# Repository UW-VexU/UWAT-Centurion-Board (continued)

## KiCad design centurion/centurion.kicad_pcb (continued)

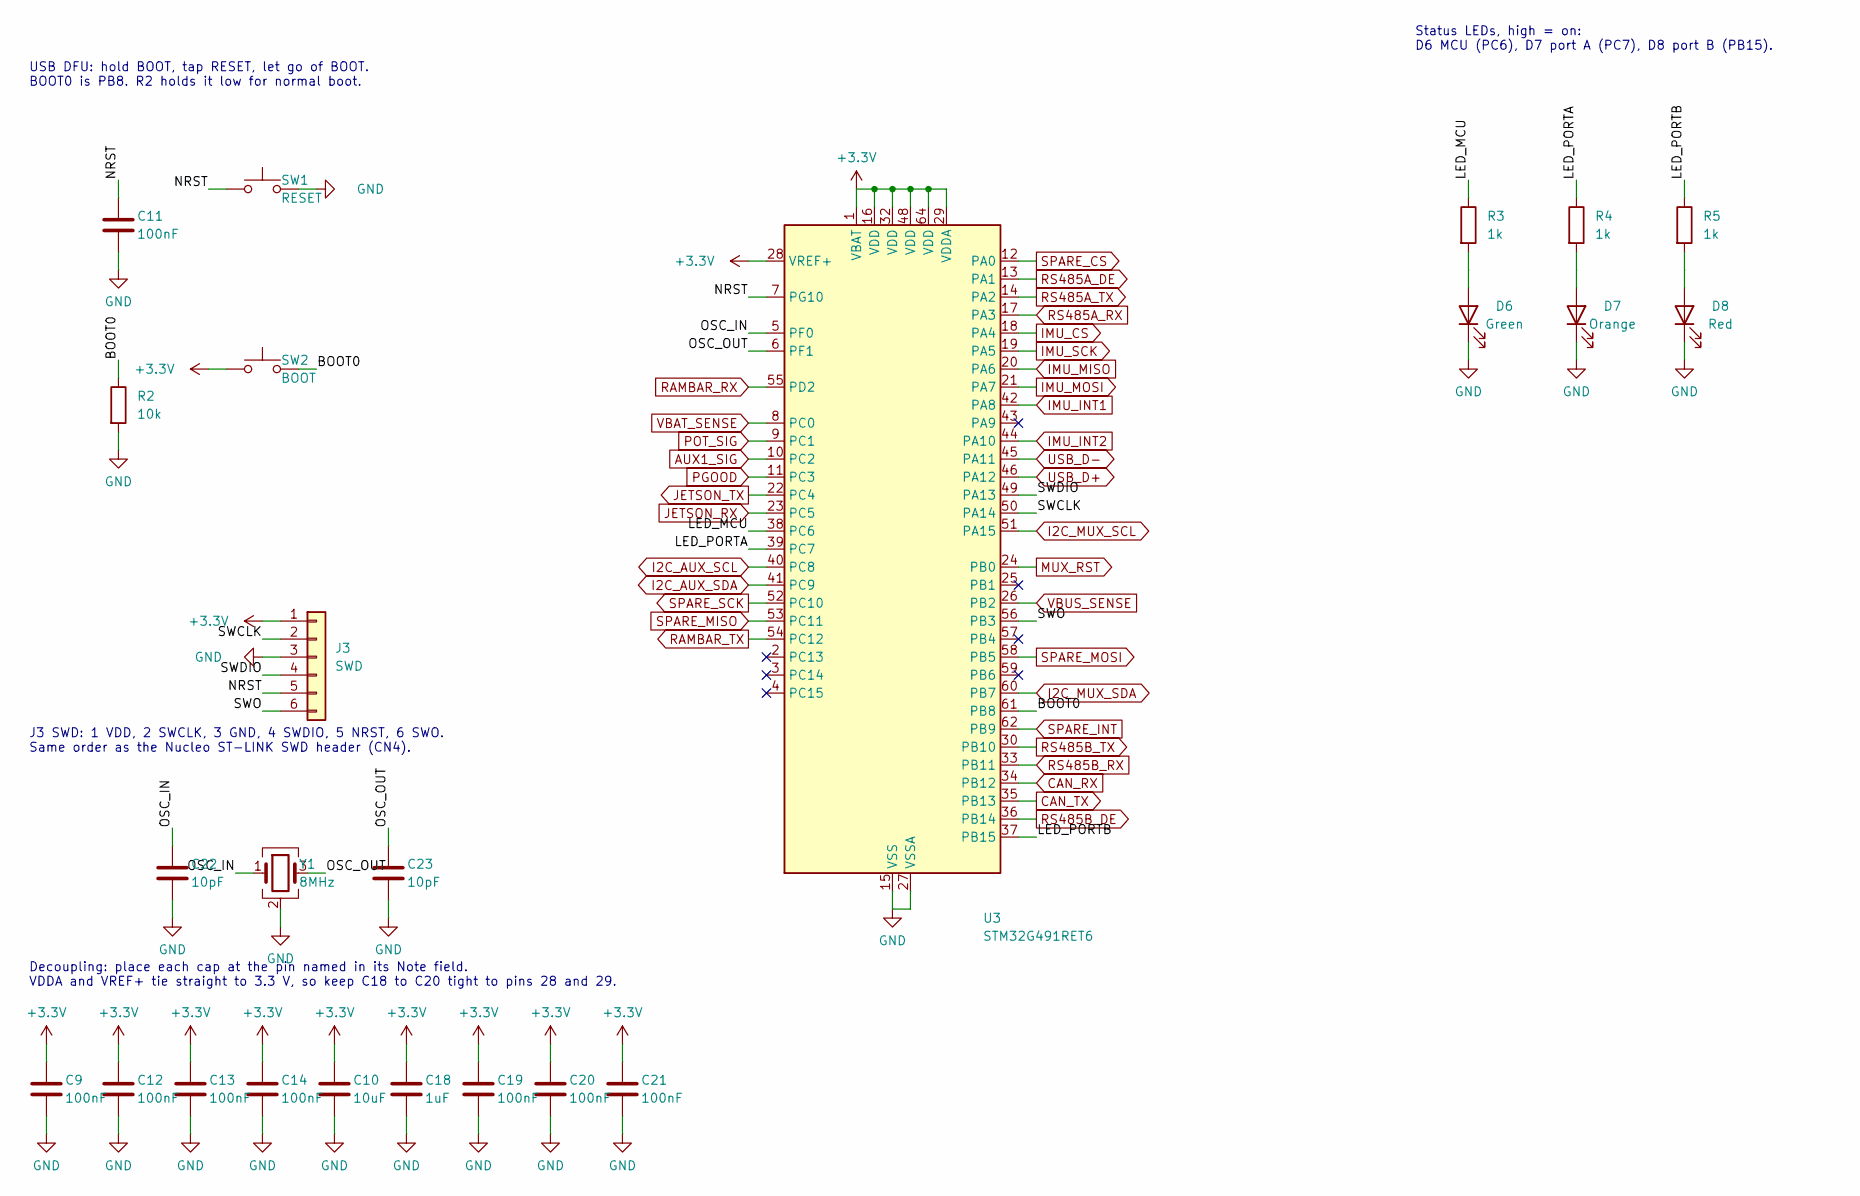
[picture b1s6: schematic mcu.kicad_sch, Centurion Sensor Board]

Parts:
C9, C11, C12, C13, C14, C19, C20, C21: 100nF; C_0805_2012Metric; MPN CC0805KRX7R9BB104
C10: 10uF; C_0805_2012Metric; MPN GRM21BR61E106KA73K
C18: 1uF; C_0805_2012Metric; MPN CC0805KKX7R8BB105
C22, C23: 10pF; C_0805_2012Metric; MPN CC0805JRNPO9BN100
D6: Green; LED_0603_1608Metric; MPN LTST-C191KGKT
D7: Orange; LED_0603_1608Metric; MPN LTST-C191KFKT
D8: Red; LED_0603_1608Metric; MPN LTST-C191KRKT
J3: SWD; PinHeader_1x06_P2.54mm_Vertical; MPN PRPC040SAAN-RC
R2: 10k; R_0805_2012Metric; MPN RC0805FR-0710KL
R3, R4, R5: 1k; R_0805_2012Metric; MPN RC0805FR-071KL
SW1: RESET; SW_SPST_TL3342; MPN TL3342F160QG
SW2: BOOT; SW_SPST_TL3342; MPN TL3342F160QG
U3: STM32G491RET6; LQFP-64_10x10mm_P0.5mm; MPN STM32G491RET6
Y1: 8MHz; Crystal_SMD_3225-4Pin_3.2x2.5mm; MPN ABM8AIG-8.000MHZ-8-V1R-T

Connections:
+3.3V: C9.1, C10.1, C12.1, C13.1, C14.1, C18.1, C19.1, C20.1, C21.1, J3.1, SW2.1, U3.1 (VBAT), U3.16 (VDD), U3.28 (VREF+), U3.29 (VDDA), U3.32 (VDD), U3.48 (VDD), U3.64 (VDD); also elsewhere on the board
/MCU/BOOT0: R2.1, SW2.2, U3.61 (PB8)
/MCU/LED_MCU: R3.1, U3.38 (PC6)
/MCU/LED_PORTA: R4.1, U3.39 (PC7)
/MCU/LED_PORTB: R5.1, U3.37 (PB15)
/MCU/NRST: C11.1, J3.5, SW1.1, U3.7 (PG10)
/MCU/OSC_IN: C22.1, U3.5 (PF0), Y1.1
/MCU/OSC_OUT: C23.1, U3.6 (PF1), Y1.3
/MCU/SWCLK: J3.2, U3.50 (PA14)
/MCU/SWDIO: J3.4, U3.49 (PA13)
/MCU/SWO: J3.6, U3.56 (PB3)
AUX1_SIG: U3.10 (PC2); also elsewhere on the board
CAN_RX: U3.34 (PB12); also elsewhere on the board
CAN_TX: U3.35 (PB13); also elsewhere on the board
GND: C9.2, C10.2, C11.2, C12.2, C13.2, C14.2, C18.2, C19.2, C20.2, C21.2, C22.2, C23.2, D6.1 (K), D7.1 (K), D8.1 (K), J3.3, R2.2, SW1.2, U3.15 (VSS), U3.27 (VSSA), U3.31 (VSS), U3.47 (VSS), U3.63 (VSS), Y1.2 (G), Y1.4 (G); also elsewhere on the board
I2C_AUX_SCL: U3.40 (PC8); also elsewhere on the board
I2C_AUX_SDA: U3.41 (PC9); also elsewhere on the board
I2C_MUX_SCL: U3.51 (PA15); also elsewhere on the board
I2C_MUX_SDA: U3.60 (PB7); also elsewhere on the board
IMU_CS: U3.18 (PA4); also elsewhere on the board
IMU_INT1: U3.42 (PA8); also elsewhere on the board
IMU_INT2: U3.44 (PA10); also elsewhere on the board
IMU_MISO: U3.20 (PA6); also elsewhere on the board
IMU_MOSI: U3.21 (PA7); also elsewhere on the board
IMU_SCK: U3.19 (PA5); also elsewhere on the board
JETSON_RX: U3.23 (PC5); also elsewhere on the board
JETSON_TX: U3.22 (PC4); also elsewhere on the board
MUX_RST: U3.24 (PB0); also elsewhere on the board
unnamed: D6.2 (A), R3.2
unnamed: D7.2 (A), R4.2
unnamed: D8.2 (A), R5.2
PGOOD: U3.11 (PC3); also elsewhere on the board
POT_SIG: U3.9 (PC1); also elsewhere on the board
RAMBAR_RX: U3.55 (PD2); also elsewhere on the board
RAMBAR_TX: U3.54 (PC12); also elsewhere on the board
RS485A_DE: U3.13 (PA1); also elsewhere on the board
RS485A_RX: U3.17 (PA3); also elsewhere on the board
RS485A_TX: U3.14 (PA2); also elsewhere on the board
RS485B_DE: U3.36 (PB14); also elsewhere on the board
RS485B_RX: U3.33 (PB11); also elsewhere on the board
RS485B_TX: U3.30 (PB10); also elsewhere on the board
SPARE_CS: U3.12 (PA0); also elsewhere on the board
SPARE_INT: U3.62 (PB9); also elsewhere on the board
SPARE_MISO: U3.53 (PC11); also elsewhere on the board
SPARE_MOSI: U3.58 (PB5); also elsewhere on the board
SPARE_SCK: U3.52 (PC10); also elsewhere on the board
USB_D+: U3.46 (PA12); also elsewhere on the board
USB_D-: U3.45 (PA11); also elsewhere on the board
VBAT_SENSE: U3.8 (PC0); also elsewhere on the board
VBUS_SENSE: U3.26 (PB2); also elsewhere on the board

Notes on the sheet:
Decoupling: place each cap at the pin named in its Note field. VDDA and VREF+ tie straight to 3.3 V, so keep C18 to C20 tight to pins 28 and 29.
USB DFU: hold BOOT, tap RESET, let go of BOOT. BOOT0 is PB8. R2 holds it low for normal boot.
J3 SWD: 1 VDD, 2 SWCLK, 3 GND, 4 SWDIO, 5 NRST, 6 SWO. Same order as the Nucleo ST-LINK SWD header (CN4).
Status LEDs, high = on: D6 MCU (PC6), D7 port A (PC7), D8 port B (PB15).

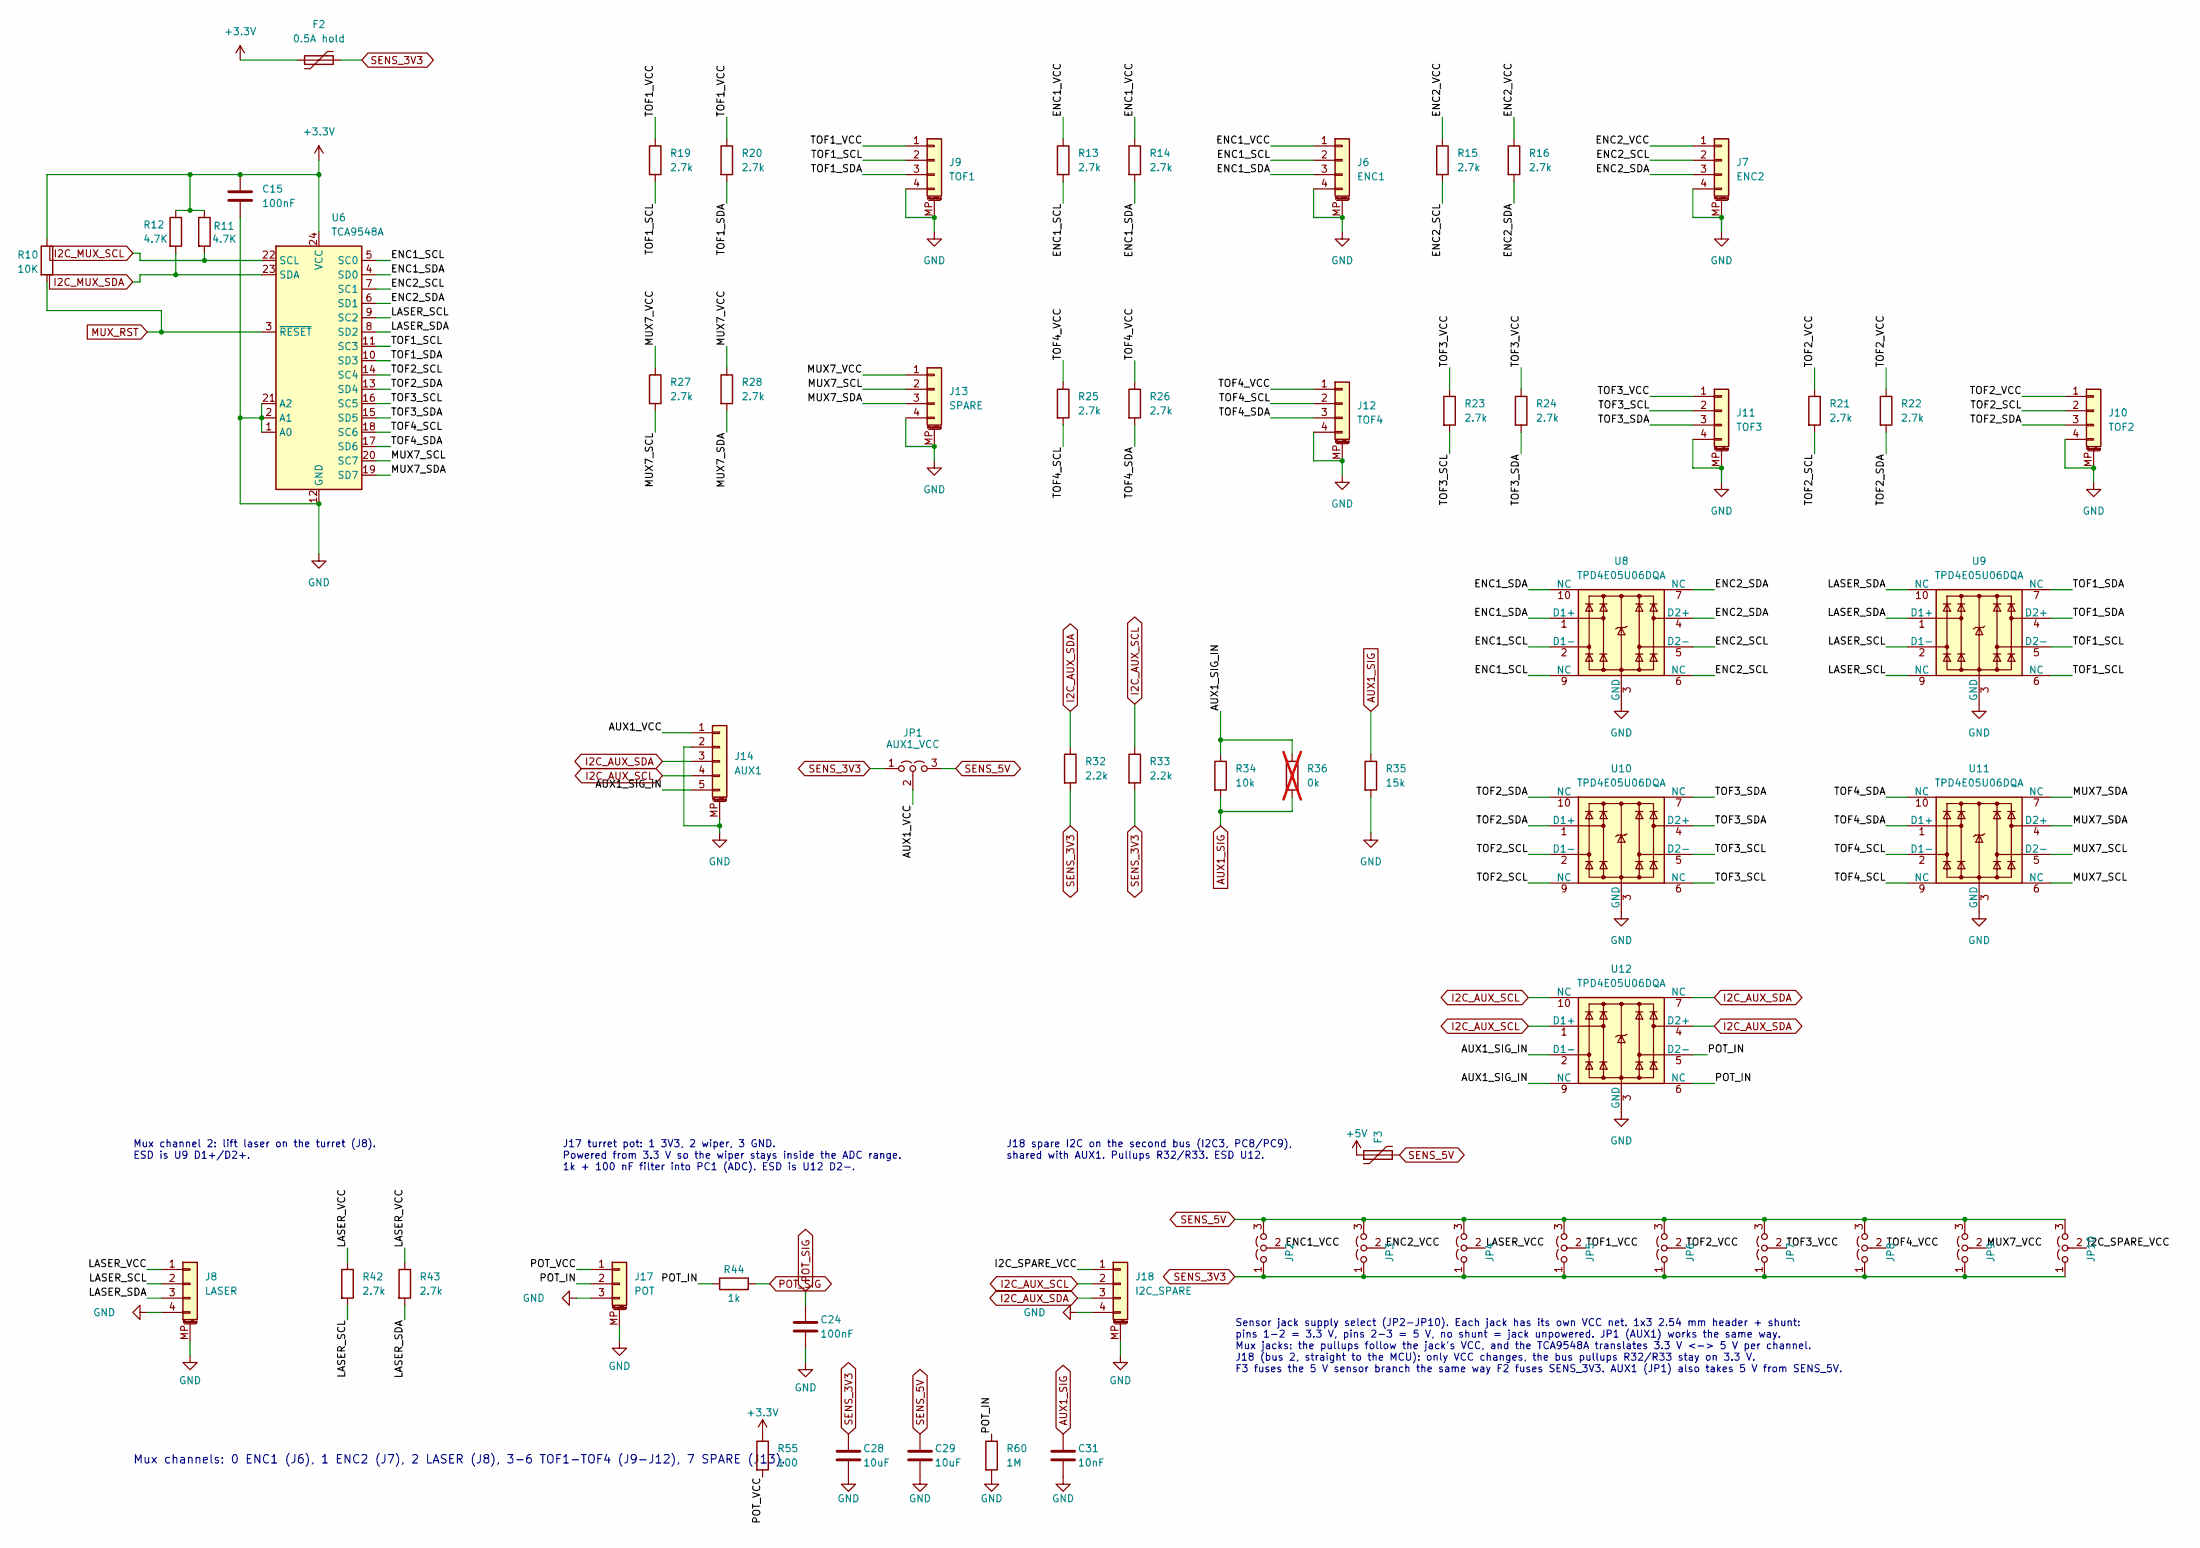
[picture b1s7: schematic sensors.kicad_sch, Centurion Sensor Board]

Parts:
C15, C24: 100nF; C_0805_2012Metric; MPN CC0805KRX7R9BB104
C28, C29: 10uF; C_0805_2012Metric; MPN GRM21BR61E106KA73K
C31: 10nF; C_0805_2012Metric; MPN CC0805KRX7R9BB103
F2, F3: 0.5A hold; Fuse_1206_3216Metric; MPN MF-NSMF050-2
J6: ENC1; JST_GH_SM04B-GHS-TB_1x04-1MP_P1.25mm_Horizontal; MPN SM04B-GHS-TB
J7: ENC2; JST_GH_SM04B-GHS-TB_1x04-1MP_P1.25mm_Horizontal; MPN SM04B-GHS-TB
J8: LASER; JST_GH_SM04B-GHS-TB_1x04-1MP_P1.25mm_Horizontal; MPN SM04B-GHS-TB
J9: TOF1; JST_GH_SM04B-GHS-TB_1x04-1MP_P1.25mm_Horizontal; MPN SM04B-GHS-TB
J10: TOF2; JST_GH_SM04B-GHS-TB_1x04-1MP_P1.25mm_Horizontal; MPN SM04B-GHS-TB
J11: TOF3; JST_GH_SM04B-GHS-TB_1x04-1MP_P1.25mm_Horizontal; MPN SM04B-GHS-TB
J12: TOF4; JST_GH_SM04B-GHS-TB_1x04-1MP_P1.25mm_Horizontal; MPN SM04B-GHS-TB
J13: SPARE; JST_GH_SM04B-GHS-TB_1x04-1MP_P1.25mm_Horizontal; MPN SM04B-GHS-TB
J14: AUX1; JST_GH_SM05B-GHS-TB_1x05-1MP_P1.25mm_Horizontal; MPN SM05B-GHS-TB
J17: POT; JST_GH_SM03B-GHS-TB_1x03-1MP_P1.25mm_Horizontal; MPN SM03B-GHS-TB
J18: I2C_SPARE; JST_GH_SM04B-GHS-TB_1x04-1MP_P1.25mm_Horizontal; MPN SM04B-GHS-TB
JP1: AUX1_VCC; PinHeader_1x03_P2.54mm_Vertical
JP2: ENC1_VCC; PinHeader_1x03_P2.54mm_Vertical
JP3: ENC2_VCC; PinHeader_1x03_P2.54mm_Vertical
JP4: LASER_VCC; PinHeader_1x03_P2.54mm_Vertical
JP5: TOF1_VCC; PinHeader_1x03_P2.54mm_Vertical
JP6: TOF2_VCC; PinHeader_1x03_P2.54mm_Vertical
JP7: TOF3_VCC; PinHeader_1x03_P2.54mm_Vertical
JP8: TOF4_VCC; PinHeader_1x03_P2.54mm_Vertical
JP9: MUX7_VCC; PinHeader_1x03_P2.54mm_Vertical
JP10: I2C_SPARE_VCC; PinHeader_1x03_P2.54mm_Vertical
R10: 10K; R_0805_2012Metric; MPN RC0805FR-0710KL
R11, R12: 4.7K; R_0805_2012Metric; MPN RC0805FR-074K7L
R13, R14, R15, R16, R19, R20, R21, R22, R23, R24, R25, R26, R27, R28, R42, R43: 2.7k; R_0805_2012Metric; MPN RC0805FR-072K7L
R32, R33: 2.2k; R_0805_2012Metric; MPN RC0805FR-072K2L
R34: 10k; R_0805_2012Metric; MPN RC0805FR-0710KL
R35: 15k; R_0805_2012Metric; MPN RC0805FR-0715KL
R36: 0k; R_0805_2012Metric; MPN RC0805JR-070RL; not fitted
R44: 1k; R_0805_2012Metric; MPN RC0805FR-071KL
R55: 100; R_0805_2012Metric; MPN RC0805FR-07100RL
R60: 1M; R_0805_2012Metric; MPN RC0805FR-071ML
U6: TCA9548A; TSSOP-24_4.4x7.8mm_P0.65mm; MPN TCA9548APWR
U8, U9, U10, U11, U12: TPD4E05U06DQA; TI_DQA_USON-10_2.5x1.0mm_P0.5mm; MPN TPD4E05U06QDQARQ1

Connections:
+3.3V: C15.1, F2.1, R10.1, R11.1, R12.1, R55.1, U6.24 (VCC); also elsewhere on the board
+5V: F3.1; also elsewhere on the board
/Sensors/AUX1_SIG_IN: J14.5, R34.1, R36.1, U12.2 (D1-), U12.9 (NC)
/Sensors/AUX1_VCC: J14.1, JP1.2 (C)
/Sensors/ENC1_SCL: J6.2, R13.2, U6.5 (SC0), U8.2 (D1-), U8.9 (NC)
/Sensors/ENC1_SDA: J6.3, R14.2, U6.4 (SD0), U8.1 (D1+), U8.10 (NC)
/Sensors/ENC1_VCC: J6.1, JP2.2 (C), R13.1, R14.1
/Sensors/ENC2_SCL: J7.2, R15.2, U6.7 (SC1), U8.5 (D2-), U8.6 (NC)
/Sensors/ENC2_SDA: J7.3, R16.2, U6.6 (SD1), U8.4 (D2+), U8.7 (NC)
/Sensors/ENC2_VCC: J7.1, JP3.2 (C), R15.1, R16.1
/Sensors/I2C_SPARE_VCC: J18.1, JP10.2 (C)
/Sensors/LASER_SCL: J8.2, R42.2, U6.9 (SC2), U9.2 (D1-), U9.9 (NC)
/Sensors/LASER_SDA: J8.3, R43.2, U6.8 (SD2), U9.1 (D1+), U9.10 (NC)
/Sensors/LASER_VCC: J8.1, JP4.2 (C), R42.1, R43.1
/Sensors/MUX7_SCL: J13.2, R27.2, U6.20 (SC7), U11.5 (D2-), U11.6 (NC)
/Sensors/MUX7_SDA: J13.3, R28.2, U6.19 (SD7), U11.4 (D2+), U11.7 (NC)
/Sensors/MUX7_VCC: J13.1, JP9.2 (C), R27.1, R28.1
/Sensors/POT_IN: J17.2, R44.1, R60.1, U12.5 (D2-), U12.6 (NC)
/Sensors/POT_VCC: J17.1, R55.2
/Sensors/TOF1_SCL: J9.2, R19.2, U6.11 (SC3), U9.5 (D2-), U9.6 (NC)
/Sensors/TOF1_SDA: J9.3, R20.2, U6.10 (SD3), U9.4 (D2+), U9.7 (NC)
/Sensors/TOF1_VCC: J9.1, JP5.2 (C), R19.1, R20.1
/Sensors/TOF2_SCL: J10.2, R21.2, U6.14 (SC4), U10.2 (D1-), U10.9 (NC)
/Sensors/TOF2_SDA: J10.3, R22.2, U6.13 (SD4), U10.1 (D1+), U10.10 (NC)
/Sensors/TOF2_VCC: J10.1, JP6.2 (C), R21.1, R22.1
/Sensors/TOF3_SCL: J11.2, R23.2, U6.16 (SC5), U10.5 (D2-), U10.6 (NC)
/Sensors/TOF3_SDA: J11.3, R24.2, U6.15 (SD5), U10.4 (D2+), U10.7 (NC)
/Sensors/TOF3_VCC: J11.1, JP7.2 (C), R23.1, R24.1
/Sensors/TOF4_SCL: J12.2, R25.2, U6.18 (SC6), U11.2 (D1-), U11.9 (NC)
/Sensors/TOF4_SDA: J12.3, R26.2, U6.17 (SD6), U11.1 (D1+), U11.10 (NC)
/Sensors/TOF4_VCC: J12.1, JP8.2 (C), R25.1, R26.1
AUX1_SIG: C31.1, R34.2, R35.1, R36.2; also elsewhere on the board
GND: C15.2, C24.2, C28.2, C29.2, C31.2, J6.4, J6.MP (MountPin), J7.4, J7.MP (MountPin), J8.4, J8.MP (MountPin), J9.4, J9.MP (MountPin), J10.4, J10.MP (MountPin), J11.4, J11.MP (MountPin), J12.4, J12.MP (MountPin), J13.4, J13.MP (MountPin), J14.2, J14.MP (MountPin), J17.3, J17.MP (MountPin), J18.4, J18.MP (MountPin), R35.2, R60.2, U6.1 (A0), U6.2 (A1), U6.12 (GND), U6.21 (A2), U8.3 (GND), U8.8 (GND), U9.3 (GND), U9.8 (GND), U10.3 (GND), U10.8 (GND), U11.3 (GND), U11.8 (GND), U12.3 (GND), U12.8 (GND); also elsewhere on the board
I2C_AUX_SCL: J14.4, J18.2, R33.1, U12.1 (D1+), U12.10 (NC); also elsewhere on the board
I2C_AUX_SDA: J14.3, J18.3, R32.1, U12.4 (D2+), U12.7 (NC); also elsewhere on the board
I2C_MUX_SCL: R11.2, U6.22 (SCL); also elsewhere on the board
I2C_MUX_SDA: R12.2, U6.23 (SDA); also elsewhere on the board
MUX_RST: R10.2, U6.3 (~RESET); also elsewhere on the board
POT_SIG: C24.1, R44.2; also elsewhere on the board
SENS_3V3: C28.1, F2.2, JP1.1 (A), JP2.1 (A), JP3.1 (A), JP4.1 (A), JP5.1 (A), JP6.1 (A), JP7.1 (A), JP8.1 (A), JP9.1 (A), JP10.1 (A), R32.2, R33.2; also elsewhere on the board
SENS_5V: C29.1, F3.2, JP1.3 (B), JP2.3 (B), JP3.3 (B), JP4.3 (B), JP5.3 (B), JP6.3 (B), JP7.3 (B), JP8.3 (B), JP9.3 (B), JP10.3 (B)

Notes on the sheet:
Mux channel 2: lift laser on the turret (J8). ESD is U9 D1+/D2+.
J17 turret pot: 1 3V3, 2 wiper, 3 GND. Powered from 3.3 V so the wiper stays inside the ADC range. 1k + 100 nF filter into PC1 (ADC). ESD is U12 D2-.
J18 spare I2C on the second bus (I2C3, PC8/PC9), shared with AUX1. Pullups R32/R33. ESD U12.
Mux channels: 0 ENC1 (J6), 1 ENC2 (J7), 2 LASER (J8), 3-6 TOF1-TOF4 (J9-J12), 7 SPARE (J13).
Sensor jack supply select (JP2-JP10). Each jack has its own VCC net. 1x3 2.54 mm header + shunt: pins 1-2 = 3.3 V, pins 2-3 = 5 V, no shunt = jack unpowered. JP1 (AUX1) works the same way. Mux jacks: the pullups follow the jack's VCC, and the TCA9548A translates 3.3 V <-> 5 V per channel. J18 (bus 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

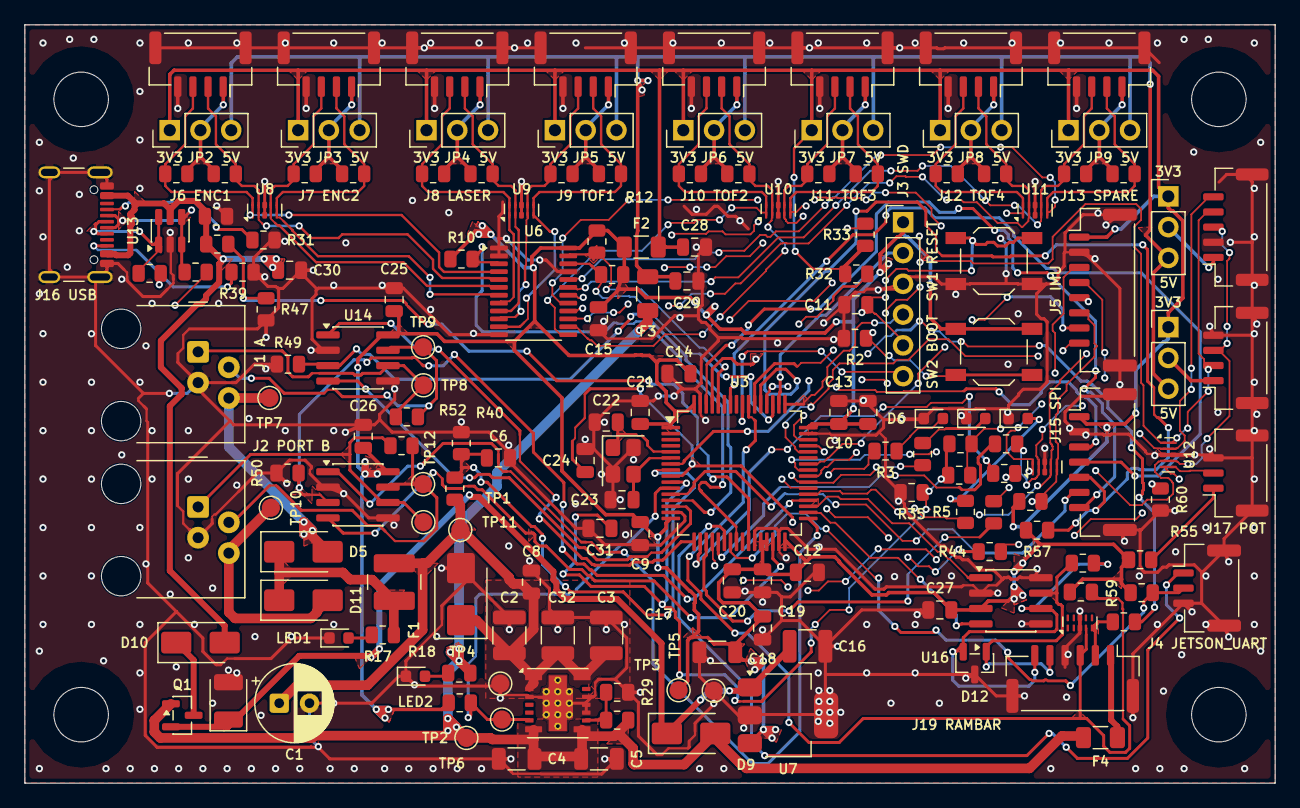
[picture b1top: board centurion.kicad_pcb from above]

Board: 4 copper layers, 103.2 x 62.6 mm, 169 parts (0 on the bottom side), 107 nets.

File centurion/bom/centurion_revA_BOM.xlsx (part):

Centurion Sensor Board, Bill of Materials, Rev A (STM32G491 + TCA9548A + TCAN33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
UWAT VEXU. DigiKey Canada stock and CAD price breaks, read from digikey.ca on N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
Boards to build |  | 6 | Edit the yellow cells. Type your own quantity in the yellow Your order qty colu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
Ref | Block | Description | Manufacturer | Mfr part number | DigiKey part number | Qty per board | Spares | Needed (boards x qty + spares) | Your order qty (optional) | Order qty | Unit price at order qty (CAD) | Order cost (CAD) | Next price break (qty) | Unit price at next break (CAD) | Tip | DigiKey stock | DigiKey Canada link | Notes | On hand (left from earlier orders) | Earlier order
C1 | Power | Aluminum electrolytic, 47 µF 50 V, 6.3 mm radial | Panasonic | EEU-FR1H470 | P124235-ND | 1 | 0 | 6 |  | 0 | 0.7 | 0 |  |  |  | 26276 | https://www.digikey.ca/en/products/detail/panasonic-industry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 |  | 8 | powerJackal
C2, C3, C16, C32 | Power | Ceramic capacitor, 10 µF 50 V X7R, 1210 | Samsung Electro-Mechanics | CL32B106KBJNNNE | 1276-3387-1-ND | 4 | 2 | 26 |  | 0 | 0.63600000000000001 | 0 |  |  |  | 742985 | https://www.digikey.ca/en/products/detail/samsung-electro-me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 | C2, C3, C32: buck input ceramics at U1 VIN (TI asks for 20 uF effective). C16: 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 | 26 | powerJackal, stellaNova
C4, C5, C17 | Power | Ceramic capacitor, 47 µF 10 V X5R, 1206 | Murata | GRM31CR61A476ME15L | 490-5528-1-ND | 3 | 2 | 20 |  | 0 | 0.36199999999999999 | 0 |  |  |  | 180907 | https://www.digikey.ca/en/products/detail/murata-electronics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 |  | 42 | powerJackal
C6, C8, C9, C11, C12, C13, C14, C15, C19, C20, C21, C24, C25, C26, C27, C30 | Power, MCU, Sensor ports, Smart ports | Ceramic capacitor, 100 nF 50 V X7R, 0805 | Yageo | CC0805KRX7R9BB104 | 311-1140-1-ND | 16 | 2 | 98 | 10 | 10 | 0.14599999999999999 | 1.46 | 50 | 0.1018 |  | 4955773 | https://www.digikey.ca/en/products/detail/yageo/CC0805KRX7R9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 | Place at NRST pin 7. Place at U14/U15 pin 8. Place at VBAT pin 1. Place at VDD 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 | 88 | powerJackal
D4 | Power | TVS diode, 16 V standoff, unidirectional, SMB | Littelfuse | SMBJ16A | SMBJ16ALFCT-ND | 1 | 1 | 7 |  | 0 | 0.79 | 0 |  |  |  | 25785 | https://www.digikey.ca/en/products/detail/littelfuse-inc/SMB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 |  | 8 | powerJackal
D9, D10 | Power | Schottky diode, 40 V 1 A, SMA | Vishay | SS14-E3/61T | SS14-E3/61TGICT-ND | 2 | 1 | 13 | 2 | 2 | 0.7 | 1.4 | 10 | 0.42499999999999999 |  | 178712 | https://www.digikey.ca/en/products/detail/vishay-general-sem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 |  | 11 | powerJackal
F1 | Power | Polyfuse, 1.5 A hold, 33 V, 2016 | Littelfuse | 2016L150/33DR | 18-2016L150/33DRCT-ND | 1 | 1 | 7 |  | 0 | 1.0980000000000001 | 0 |  |  |  | 29235 | https://www.digikey.ca/en/products/detail/littelfuse-inc/201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 |  | 8 | powerJackal
J16 | Power | USB-C receptacle, USB 2.0, 16 pin | GCT | USB4105-GF-A | 2073-USB4105-GF-ACT-ND | 1 | 0 | 6 |  | 0 | 1.19 | 0 |  |  |  | 85103 | https://www.digikey.ca/en/products/detail/gct/USB4105-GF-A/11198441 |  | 15 | powerJackal, stellaNova
Q1 | Power | P-channel MOSFET, -30 V, SOT-23 (USB power switch) | Alpha & Omega Semiconductor | AO3401A | 785-1001-1-ND | 1 | 1 | 7 |  | 0 | 0.82 | 0 |  |  |  | 319128 | https://www.digikey.ca/en/products/detail/alpha-omega-semico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 | USB power switch. On only while the 5 V rail is down, so USB powers the board o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 | 8 | powerJackal
R1 | Power | Resistor, 100 kΩ 1%, 0805 | Yageo | RC0805FR-07100KL | 311-100KCRCT-ND | 1 | 2 | 8 | 25 | 25 | 4.48E-2 | 1.1199999999999999 | 50 | 3.6799999999999999E-2 |  | 357376 | https://www.digikey.ca/en/products/detail/yageo/RC0805FR-071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 |  | 0
R18, R32, R33 | Power, Sensor ports | Resistor, 2.2 kΩ 1%, 0805 | Yageo | RC0805FR-072K2L | 311-2.20KCRCT-ND | 3 | 2 | 20 |  | 0 | 5.3999999999999999E-2 | 0 |  |  |  | 374622 | https://www.digikey.ca/en/products/detail/yageo/RC0805FR-072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 | R18: LED2. R32, R33: bus 2 (I2C3) pullups, 2.2k so two cables still meet 400 kH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 | 98 | powerJackal
R29 | Power | Resistor, 2.49 kΩ 1%, 0805 (5 V feedback) | Yageo | RC0805FR-072K49L | 311-2.49KCRCT-ND | 1 | 2 | 8 |  | 0 | 0.17 | 0 |  |  |  | 1178164 | https://www.digikey.ca/en/products/detail/yageo/RC0805FR-072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 | RFBB, sets 5.0 V | 108 | powerJackal
R31, R37, R48 | Power | Resistor, 5.1 kΩ 1%, 0805 | Stackpole Electronics | RMCF0805FT5K10 | RMCF0805FT5K10CT-ND | 3 | 2 | 20 |  | 0 | 4.2999999999999997E-2 | 0 |  |  |  | 98354 | https://www.digikey.ca/en/products/detail/stackpole-electron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 |  | 246 | powerJackal
R40 | Power | Resistor, 22 kΩ 1%, 0805 | Yageo | RC0805FR-0722KL | 311-22.0KCRCT-ND | 1 | 2 | 8 | 25 | 25 | 4.48E-2 | 1.1199999999999999 | 50 | 3.6799999999999999E-2 |  | 186895 | https://www.digikey.ca/en/products/detail/yageo/RC0805FR-072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 | Battery sense, 100k over 22k: 3.3 V full scale is 18.3 V. | 0
U1 | Power | 5 V step-down power module, 2 A, B3QFN-14 | Texas Instruments | TPSM53602RDAR | 296-TPSM53602RDARCT-ND | 1 | 0 | 6 | 3 | 3 | 11.13 | 33.39 | 5 | 10.72 |  | 2786 | https://www.digikey.ca/en/products/detail/texas-instruments/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 | EN tied to VIN. DNC pins 4, 5 and V5V (13) stay unconnected. | 3 | powerJackal
U7 | Power | LDO regulator, 3.3 V 1 A, SOT-223 | Microchip Technology | MCP1826ST-3302E/DB | MCP1826ST-3302E/DBCT-ND | 1 | 0 | 6 |  | 0 | 1.44 | 0 |  |  |  | 39535 | https://www.digikey.ca/en/products/detail/microchip-technolo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 | Drawn with the AP7361C-33E symbol. Same SOT-223 pinout: 1 IN, 2 GND and tab, 3 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 | 8 | powerJackal
U13 | Power | USB ESD protection, SOT-23-6 | STMicroelectronics | USBLC6-2SC6 | 497-5235-1-ND | 1 | 1 | 7 |  | 0 | 0.8 | 0 |  |  |  | 63343 | https://www.digikey.ca/en/products/detail/stmicroelectronics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 |  | 15 | powerJackal, stellaNova
D5, D11 | Smart ports | Schottky diode, 40 V 3 A, SMA (smart port OR diodes) | Diodes Incorporated | B340A-13-F | B340A-FDICT-ND | 2 | 1 | 13 |  | 0 | 0.497 | 0 |  |  |  | 254159 | https://www.digikey.ca/en/products/detail/diodes-incorporate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 |  | 21 | powerJackal
J1, J2 | Smart ports | Smart port jack, 4P4C modular, right angle, through hole | Molex | 0955012441 | WM5568-ND | 2 | 0 | 12 |  | 0 | 1.2929999999999999 | 0 |  |  |  | 4151 | https://www.digikey.ca/en/products/detail/molex/0955012441/1835860 | Pin map assumes the usual black, red, green, yellow order. Check with a meter. | 15 | powerJackal, stellaNova
U14, U15 | Smart ports | RS-485 transceiver, half duplex, 3.3 V, ±65 V fault protected, 2 Mbps, SOIC-8 | Analog Devices | MAX33071EASA+ | 505-MAX33071EASA+-ND | 2 | 0 | 12 | 5 | 5 | 12.3 | 61.5 | 10 | 9.5039999999999996 |  | 2946 | https://www.digikey.ca/en/products/detail/analog-devices-inc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 | RE tied low: the receiver is always on, so the MCU hears its own echo when send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 | 7 | stellaNova
C10, C28, C29 | MCU, Sensor ports | Ceramic capacitor, 10 µF 25 V X5R, 0805 | Murata | GRM21BR61E106KA73K | 490-16824-1-ND | 3 | 2 | 20 | 11 | 11 | 0.14099999999999999 | 1.5509999999999999 | 50 | 9.98E-2 |  | 88143 | https://www.digikey.ca/en/products/detail/murata-electronics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 | C10: bulk at U3. C28, C29: bulk on SENS_3V3 and SENS_5V after F2/F3. | 9 | stellaNova
C18 | MCU | Ceramic capacitor, 1 µF 25 V X7R, 0805 | Yageo | CC0805KKX7R8BB105 | 311-1456-1-ND | 1 | 2 | 8 |  | 0 | 0.42 | 0 |  |  |  | 327549 | https://www.digikey.ca/en/products/detail/yageo/CC0805KKX7R8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 | Place at VDDA pin 29 | 18 | powerJackal
D6, LED1, LED2 | MCU, Power | LED, green, 0603 | Lite-On | LTST-C191KGKT | 160-1446-1-ND | 3 | 2 | 20 | 13 | 13 | 0.16500000000000001 | 2.145 | 100 | 0.1132 |  | 2712898 | https://www.digikey.ca/en/products/detail/liteon/LTST-C191KG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 |  | 7 | stellaNova
D7 | MCU | LED, orange, 0603 | Lite-On | LTST-C191KFKT | 160-1445-1-ND | 1 | 2 | 8 | 1 | 1 | 0.22 | 0.22 | 10 | 0.155 |  | 195728 | https://www.digikey.ca/en/products/detail/liteon/LTST-C191KF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 |  | 7 | stellaNova
D8 | MCU | LED, red, 0603 | Lite-On | LTST-C191KRKT | 160-1447-1-ND | 1 | 2 | 8 | 1 | 1 | 0.24 | 0.24 | 10 | 0.16500000000000001 |  | 1354761 | https://www.digikey.ca/en/products/detail/liteon/LTST-C191KR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 |  | 7 | stellaNova
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
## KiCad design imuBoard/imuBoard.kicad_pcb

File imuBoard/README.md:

# centurion IMU board (imuBoard)

A small board that carries a Bosch BMI270 IMU. It plugs into centurion's J5 with a straight JST GH 8-pin cable. Designed 2026-11-04, rev 1.0.

| | |
|---|---|
| Size | 38 x 24 mm, 2 layers, 1.6 mm, GND pour on both sides |
| Mounting | Two #8-32 holes (4.5 mm), 25.4 mm (1 in) apart, so they land on VEX's 0.5 in hole grid. Not tied to GND, with a 5 mm copper keepout for the screw heads |
| IMU | U1 Bosch BMI270, 4-wire SPI, 10 MHz max |
| Connector | J1 JST GH 8-pin, vertical (BM08B-GHS-TBT, the same jack as centurion J5) |
| Parts cost | $9.39 per board; $47.69 for 4 boards plus spares ([bom/](bom/)) |
| Checks | ERC 0, DRC 0, schematic parity 0, 0 unconnected (KiCad 10.0.8, 2026-11-04) |

## Connector J1

The pinout matches centurion J5 pin for pin, so the cable is straight through (pin n to pin n). Keep it 30 cm or less: see [centurion/sim/README.md](../centurion/sim/README.md#connector-simulations). JST's pre-crimped 305 mm leads (AGHGH28K305) are exactly that long, and need no crimping. The cable parts are on centurion's BOM, Cables and tools tab.

| Pin | Signal | On the board |
|---|---|---|
| 1 | 3V3 | From centurion's SENS_3V3 (fused by F2). C3 1 uF bulk, C1 and C2 100 nF at the IMU |
| 2 | GND | |
| 3 | SCK | U2 ESD, then U1 SCx |
| 4 | MOSI | U2 ESD, then U1 SDx |
| 5 | MISO | U2 ESD, then R1 100 Ω, then U1 SDO |
| 6 | CS | U2 ESD, then U1 CSB. Centurion's R58 holds it high |
| 7 | INT1 | U1 INT1 (pin 4) |
| 8 | INT2 | U1 INT2 (pin 9) |

## Parts

| Ref | Part | Why |
|---|---|---|
| U1 | BMI270 (Bosch), LGA-14 2.5 x 3 mm | Chosen 2026-11-04. The ICM-42688-P, IIM-42652, ICM-45686 and ISM330DHCX were all out of stock at DigiKey Canada. The LSM6DSV16X was the other in-stock option (lower gyro noise, but $2.40 more). ASDx, ASCx, OCSB and OSDO are unconnected, as the datasheet allows |
| U2 | TPD4E05U06QDQARQ1 (TI) | ESD clamp on SCK, MOSI, MISO and CS, right at the jack. The same part as centurion U5. Flow-through: the traces run over pins 6, 7, 9 and 10, which are not connected inside |
| R1 | 100 Ω, 0805 | MISO series resistor at the IMU, matching centurion's R8, R9 and R41 on the other three lines |
| C1, C2 | 100 nF, 0805 | VDD (pin 8) and VDDIO (pin 5), each at its pin |
| C3 | 1 uF, 0805 | Bulk at the board input |
| H1, H2 | #8-32 holes | Not parts |

Every part except the BMI270 is already on centurion's BOM.

## Axes

The top silkscreen shows them next to H1: **+X toward J1, +Y toward H2, +Z up out of the board.** U1 is turned 180 degrees on the board, so this is the datasheet's frame (section 8.2) rotated. Firmware should use these printed directions, and remap to the robot's frame from how the board is mounted.

## Why R1 is there

R1 was sized with centurion's SPI simulation (`centurion/sim/spi_imu.cir`, J5 with 100 Ω R8/R9/R41, 10 MHz, BMI270 data 30 ns after SCK). In the deck, R1 adds to the IMU's output resistance (`ROIMU = 40 + R1`).

| R1 | MISO peak at centurion | Worst MISO crosstalk | 0.5 m at the fastest GPIO speed | MISO setup margin |
|---|---|---|---|---|
| none | 4.6 to 5.0 V | 0.92 V | fails (extra SCK edges) | 8.8 to 10.9 ns |
| 33 Ω | 4.0 to 4.1 V | 0.67 V | passes | 8.6 to 10.5 ns |
| **100 Ω (fitted)** | 3.3 to 3.6 V | 0.50 V | passes | 7.5 to 9.9 ns |

So with R1 fitted, every case up to 0.5 m passes. Keep the cable 30 cm or less anyway, and SPI1's GPIO speed low, as centurion's README says.

## Firmware notes

- **SPI:** mode 0 or 3, 10 MHz or less. Set SPI1's pins to GPIO speed low (OSPEEDR 00).
- **Start-up:** the BMI270 powers up in I2C mode. One dummy SPI read switches it to SPI. Then upload Bosch's 8 kB configuration file (`INIT_CTRL = 0`, burst-write `INIT_DATA`, `INIT_CTRL = 1`, wait for `INTERNAL_STATUS`) after every power-up. Bosch's BMI270 Sensor API (boschsensortec on GitHub) includes the config file and this sequence.
- **Interrupts:** INT1 and INT2 are push-pull outputs once configured. Map data-ready to INT1 (J5 pin 7).
- **Hot-plug:** plug the cable in with centurion off. A breakout plugged into a live jack dips SENS_3V3 (centurion/sim/README.md).

## Assembly

- **U1:** a land grid array with no leads, so solder it with paste and reflow or hot air, not an iron. The footprint is KiCad's Bosch LGA-14. Its pads are a little longer than Bosch's recommended 0.475 mm, which makes paste and rework easier.
- **U2:** the same 0.5 mm-pitch USON as on centurion.
- **The rest:** 0805 parts and the GH jack can be hand soldered.

## Files

| File | What it is |
|---|---|
| `imuBoard.kicad_pro`, `.kicad_sch`, `.kicad_pcb` | The KiCad 10 project. Design rules copied from centurion |
| `lib/imuBoard.kicad_sym` | BMI270 symbol, which uses the BMI160's pinout and package |
| `lib/imuBoard.pretty/` | The TPD4E05U06 DQA footprint (from centurion) and the axis graphic |
| `bom/imuBoard_revA_BOM.xlsx`, `bom/imuBoard_revA_DigiKey_upload.csv` | BOM in the centurion / powerJackal / stellaNova format, DigiKey Canada prices and stock from 2026-11-04 |
| `docs/` | 3D renders and the schematic as PDF and SVG |
| `tools/gen_imu.py` | Generated the library, schematic and board. **Rerunning it overwrites them**, so once the board is edited by hand in KiCad, stop using it |
| `tools/build_bom.py` | Builds the BOM files (needs `openpyxl`) |

## Before ordering

- **Footprint check:** run `pcb-footprint-checker` on this folder. Pay most attention to U1's pin 1 and orientation and U2's pin order.
- **Mounting position:** decide where it bolts on. Close to the robot's turning centre and on a stiff plate is best; foam tape under it helps with vibration.
- **Board name:** "CENTURION IMU" on the back is a working name. Rename it before ordering if the team wants one in the ramBar / stellaNova style.

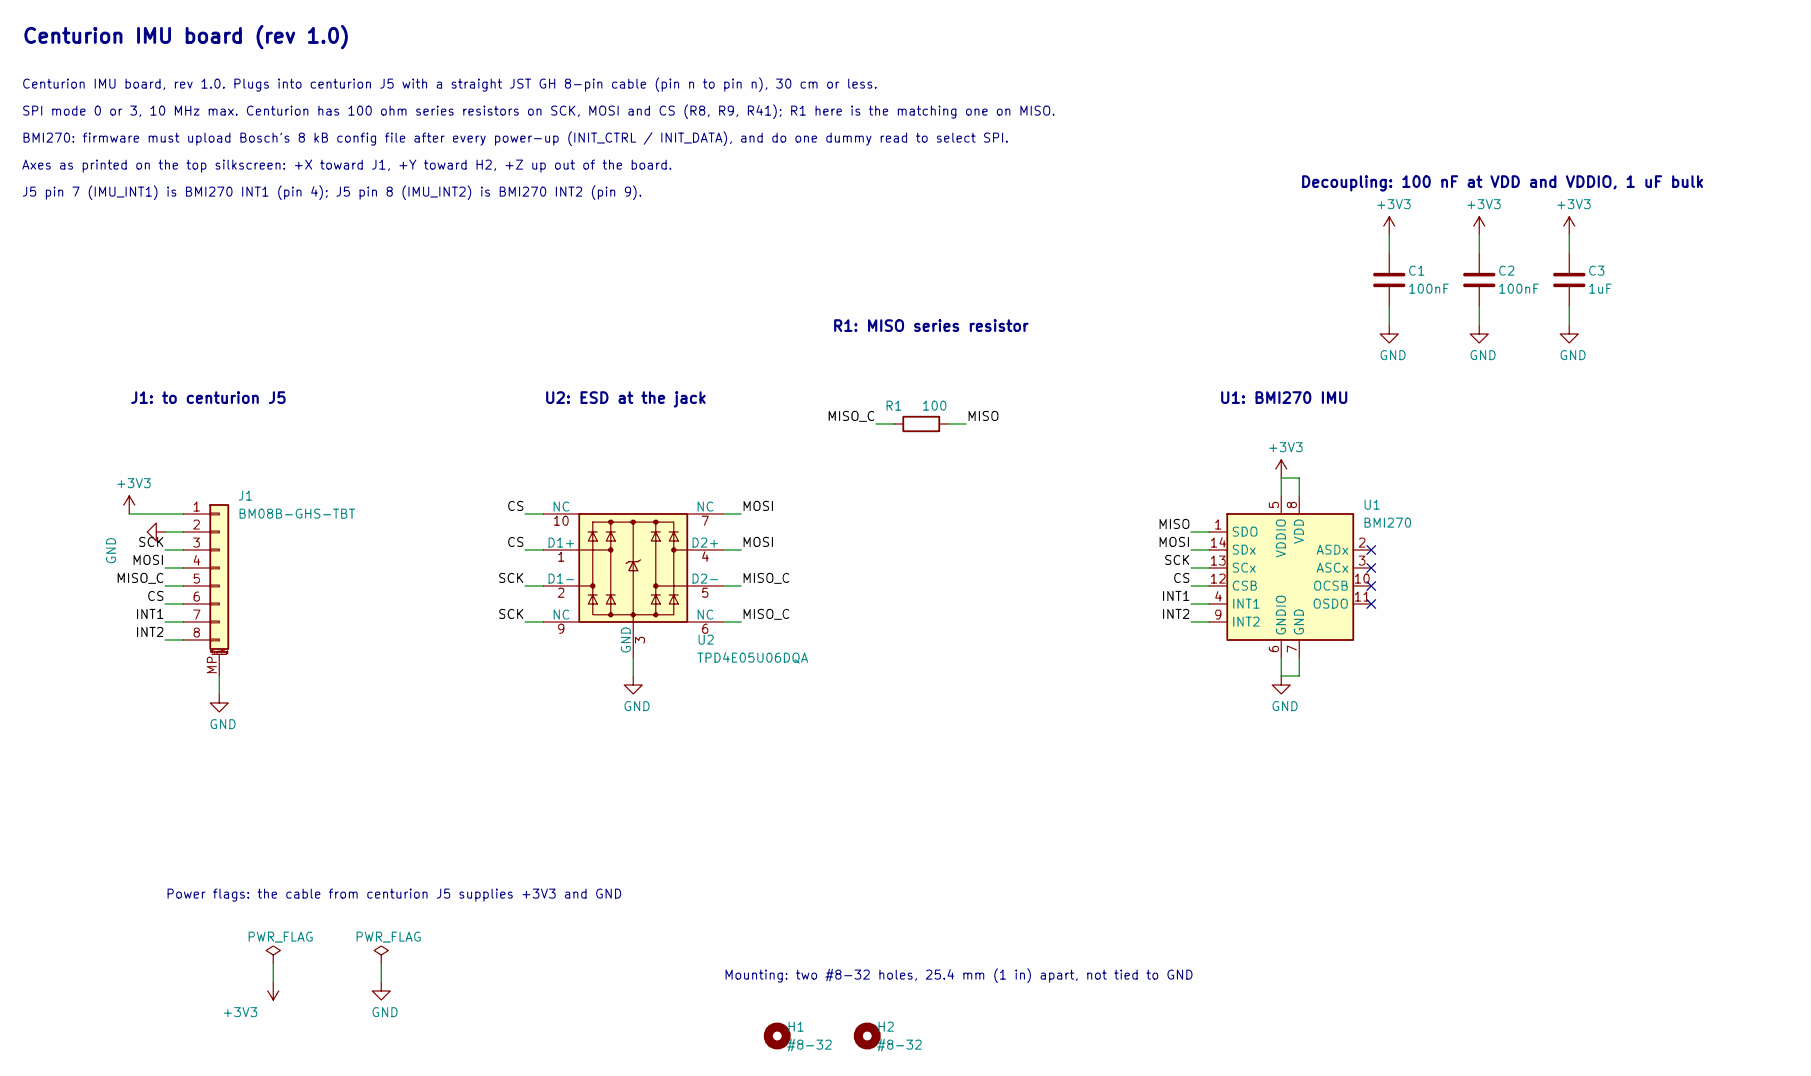
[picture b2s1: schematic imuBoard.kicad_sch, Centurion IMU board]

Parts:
C1, C2: 100nF; C_0805_2012Metric; MPN CC0805KRX7R9BB104
C3: 1uF; C_0805_2012Metric; MPN CC0805KKX7R8BB105
H1, H2: #8-32; MountingHole_4.5mm_8-32
J1: BM08B-GHS-TBT; JST_GH_BM08B-GHS-TBT_1x08-1MP_P1.25mm_Vertical; MPN BM08B-GHS-TBT
R1: 100; R_0805_2012Metric; MPN RC0805FR-07100RL
U1: BMI270; Bosch_LGA-14_3x2.5mm_P0.5mm; MPN BMI270
U2: TPD4E05U06DQA; TI_DQA_USON-10_2.5x1.0mm_P0.5mm; MPN TPD4E05U06QDQARQ1

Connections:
+3V3: C1.1, C2.1, C3.1, J1.1, U1.5 (VDDIO), U1.8 (VDD)
/CS: J1.6, U1.12 (CSB), U2.1 (D1+), U2.10 (NC)
/INT1: J1.7, U1.4 (INT1)
/INT2: J1.8, U1.9 (INT2)
/MISO: R1.2, U1.1 (SDO)
/MISO_C: J1.5, R1.1, U2.5 (D2-), U2.6 (NC)
/MOSI: J1.4, U1.14 (SDx), U2.4 (D2+), U2.7 (NC)
/SCK: J1.3, U1.13 (SCx), U2.2 (D1-), U2.9 (NC)
GND: C1.2, C2.2, C3.2, J1.2, J1.MP (MountPin), U1.6 (GNDIO), U1.7 (GND), U2.3 (GND), U2.8 (GND)

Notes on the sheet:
Power flags: the cable from centurion J5 supplies +3V3 and GND
Mounting: two #8-32 holes, 25.4 mm (1 in) apart, not tied to GND
Centurion IMU board (rev 1.0)
Centurion IMU board, rev 1.0. Plugs into centurion J5 with a straight JST GH 8-pin cable (pin n to pin n), 30 cm or less.
SPI mode 0 or 3, 10 MHz max. Centurion has 100 ohm series resistors on SCK, MOSI and CS (R8, R9, R41); R1 here is the matching one on MISO.
BMI270: firmware must upload Bosch's 8 kB config file after every power-up (INIT_CTRL / INIT_DATA), and do one dummy read to select SPI.
Axes as printed on the top silkscreen: +X toward J1, +Y toward H2, +Z up out of the board.
J5 pin 7 (IMU_INT1) is BMI270 INT1 (pin 4); J5 pin 8 (IMU_INT2) is BMI270 INT2 (pin 9).
J1: to centurion J5
U2: ESD at the jack
R1: MISO series resistor
U1: BMI270 IMU
Decoupling: 100 nF at VDD and VDDIO, 1 uF bulk

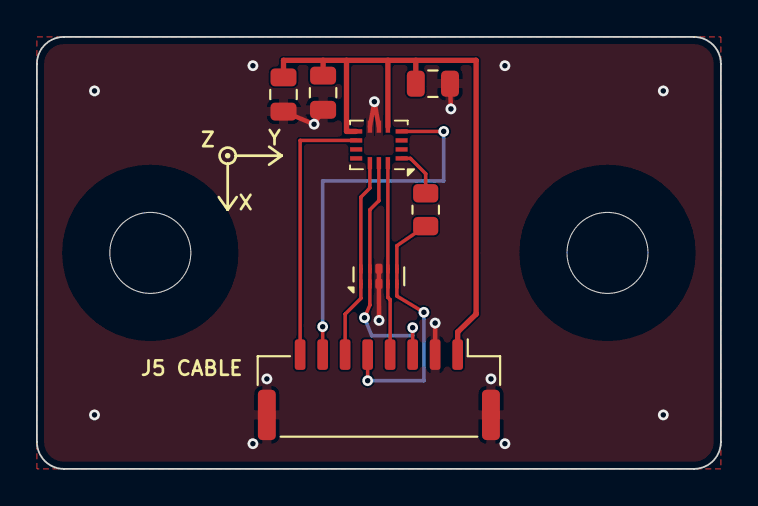
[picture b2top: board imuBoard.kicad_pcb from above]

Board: 2 copper layers, 38.0 x 24.0 mm, 10 parts (0 on the bottom side), 9 nets.

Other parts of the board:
AX1: AXES
